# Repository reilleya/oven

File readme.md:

# Oven Controller
This repository contains the KiCAD PCB design and rust firmware for an oven controller intended for use in custom composite curing ovens.

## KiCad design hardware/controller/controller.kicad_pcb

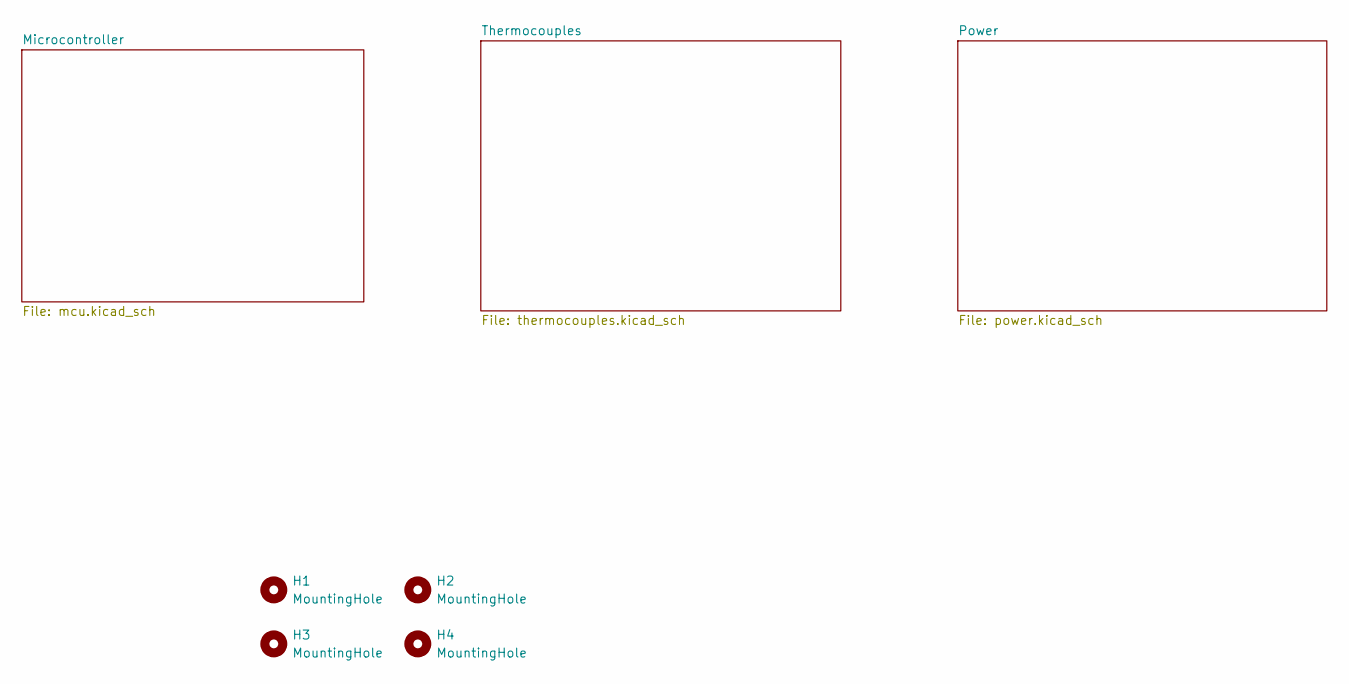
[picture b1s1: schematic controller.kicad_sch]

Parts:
H1, H2, H3, H4: MountingHole; MountingHole_2.2mm_M2_ISO14580_Pad

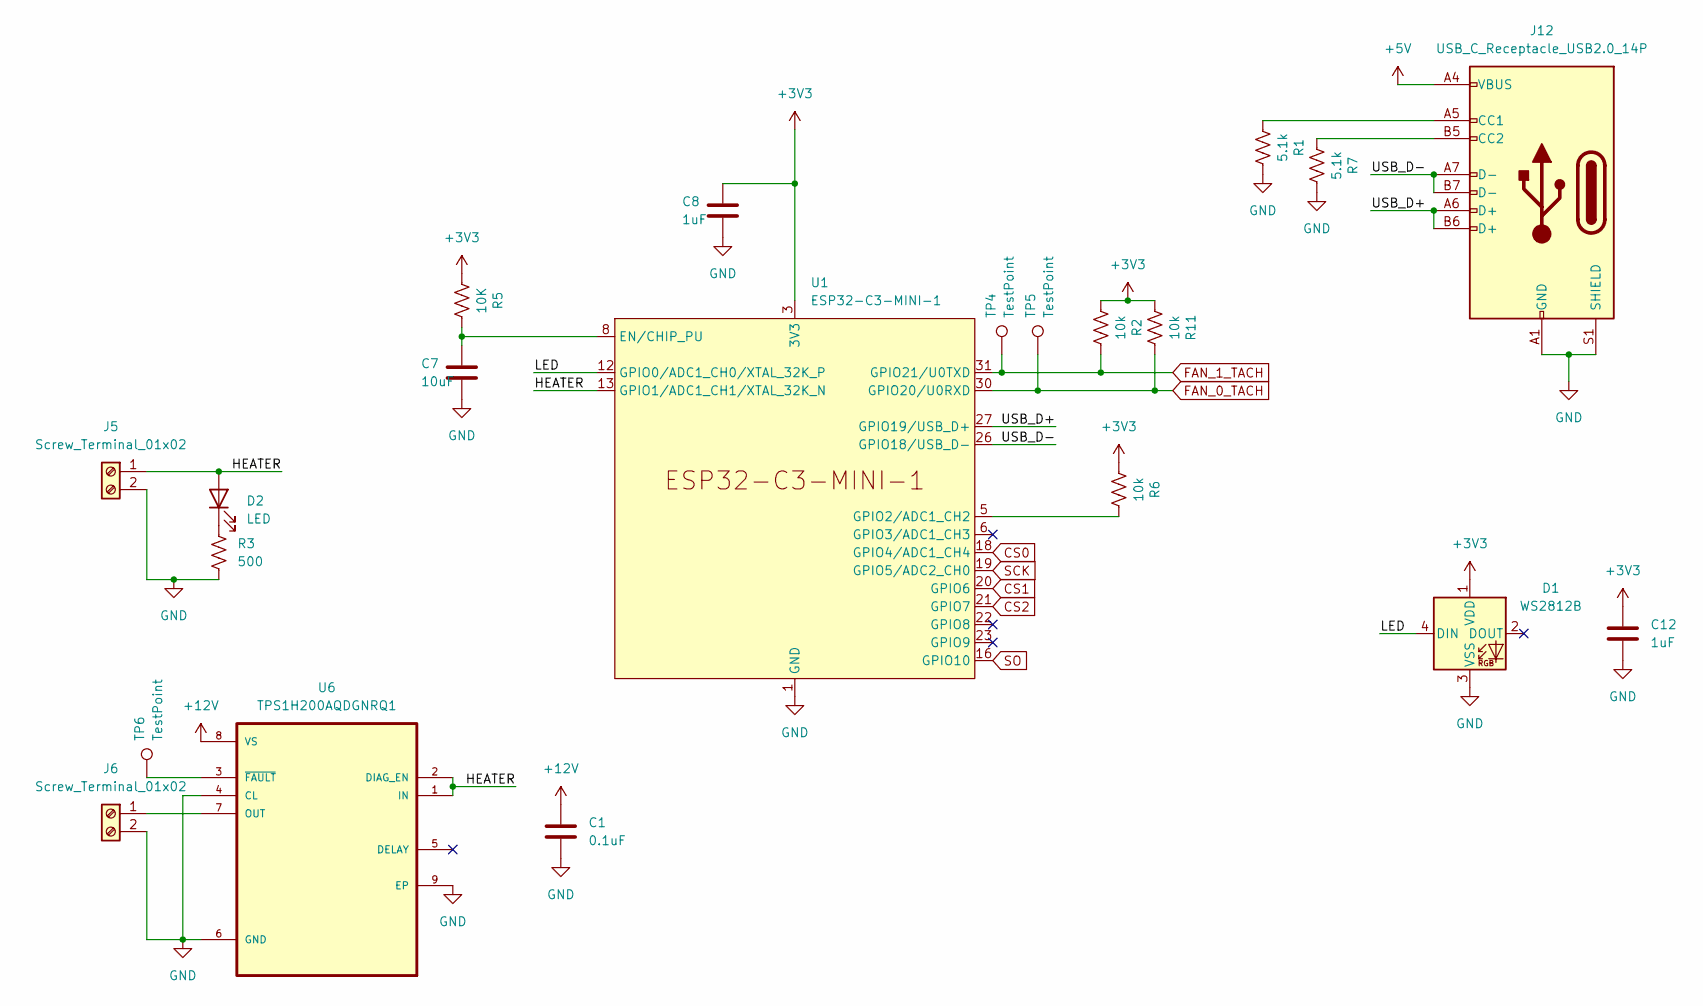
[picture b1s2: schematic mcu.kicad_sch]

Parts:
C1: 0.1uF; C_0805_2012Metric; LCSC C49678
C7: 10uF; C_0805_2012Metric; LCSC` C15850
C8, C12: 1uF; C_0805_2012Metric; LCSC C28323
D1: WS2812B; LED_WS2812B_PLCC4_5.0x5.0mm_P3.2mm; LCSC C2874885
D2: LED; LED_0805_2012Metric; LCSC C84256
J5, J6: Screw_Terminal_01x02; TerminalBlock_4Ucon_1x02_P3.50mm_Horizontal
J12: USB_C_Receptacle_USB2.0_14P; USB_C_Receptacle_GCT_USB4105-xx-A_16P_TopMnt_Horizontal; LCSC C2765186
R1, R7: 5.1k; R_0805_2012Metric; LCSC C27834
R2, R6, R11: 10k; R_0805_2012Metric; LCSC C84376
R3: 500; R_0805_2012Metric; LCSC C2828857
R5: 10K; R_0805_2012Metric; LCSC C84376
TP4, TP5, TP6: TestPoint; TestPoint_THTPad_2.0x2.0mm_Drill1.0mm
U1: ESP32-C3-MINI-1; LCSC C2838502
U6: TPS1H200AQDGNRQ1; SOP65P490X110-9N; LCSC C2653785

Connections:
+3V3: C8.1, C12.1, D1.1 (VDD), R2.2, R5.2, R6.2, R11.2, U1.3 (3V3); also elsewhere on the board
+5V: J12.A4 (VBUS), J12.A9 (VBUS), J12.B4 (VBUS), J12.B9 (VBUS); also elsewhere on the board
+12V: C1.1, U6.8 (VS); also elsewhere on the board
/Microcontroller/HEATER: D2.2 (A), J5.1, U1.13 (GPIO1/ADC1_CH1/XTAL_32K_N), U6.1 (IN), U6.2 (DIAG_EN)
/Microcontroller/LED: D1.4 (DIN), U1.12 (GPIO0/ADC1_CH0/XTAL_32K_P)
/Microcontroller/USB_D+: J12.A6 (D+), J12.B6 (D+), U1.27 (GPIO19/USB_D+)
/Microcontroller/USB_D-: J12.A7 (D-), J12.B7 (D-), U1.26 (GPIO18/USB_D-)
CS0: U1.18 (GPIO4/ADC1_CH4); also elsewhere on the board
CS1: U1.20 (GPIO6); also elsewhere on the board
CS2: U1.21 (GPIO7); also elsewhere on the board
FAN_0_TACH: R11.1, TP5.1, U1.30 (GPIO20/U0RXD); also elsewhere on the board
FAN_1_TACH: R2.1, TP4.1, U1.31 (GPIO21/U0TXD); also elsewhere on the board
GND: C1.2, C7.2, C8.2, C12.2, D1.3 (VSS), J5.2, J6.2, J12.A1 (GND), J12.A12 (GND), J12.B1 (GND), J12.B12 (GND), J12.S1 (SHIELD), R1.1, R3.2, R7.1, U1.1 (GND), U1.2 (GND), U1.11 (GND), U1.14 (GND), U1.36 (GND), U1.37 (GND), U1.38 (GND), U1.39 (GND), U1.40 (GND), U1.41 (GND), U1.42 (GND), U1.43 (GND), U1.44 (GND), U1.45 (GND), U1.46 (GND), U1.47 (GND), U1.48 (GND), U1.49 (GND), U1.50 (GND), U1.51 (GND), U1.52 (GND), U1.53 (GND), U6.4 (CL), U6.6 (GND), U6.9 (EP); also elsewhere on the board
unnamed: D2.1 (K), R3.1
unnamed: J6.1, U6.7 (OUT)
unnamed: J12.A5 (CC1), R1.2
unnamed: J12.B5 (CC2), R7.2
unnamed: C7.1, R5.1, U1.8 (EN/CHIP_PU)
unnamed: R6.1, U1.5 (GPIO2/ADC1_CH2)
unnamed: TP6.1, U6.3 (~FAULT)
SCK: U1.19 (GPIO5/ADC2_CH0); also elsewhere on the board
SO: U1.16 (GPIO10); also elsewhere on the board

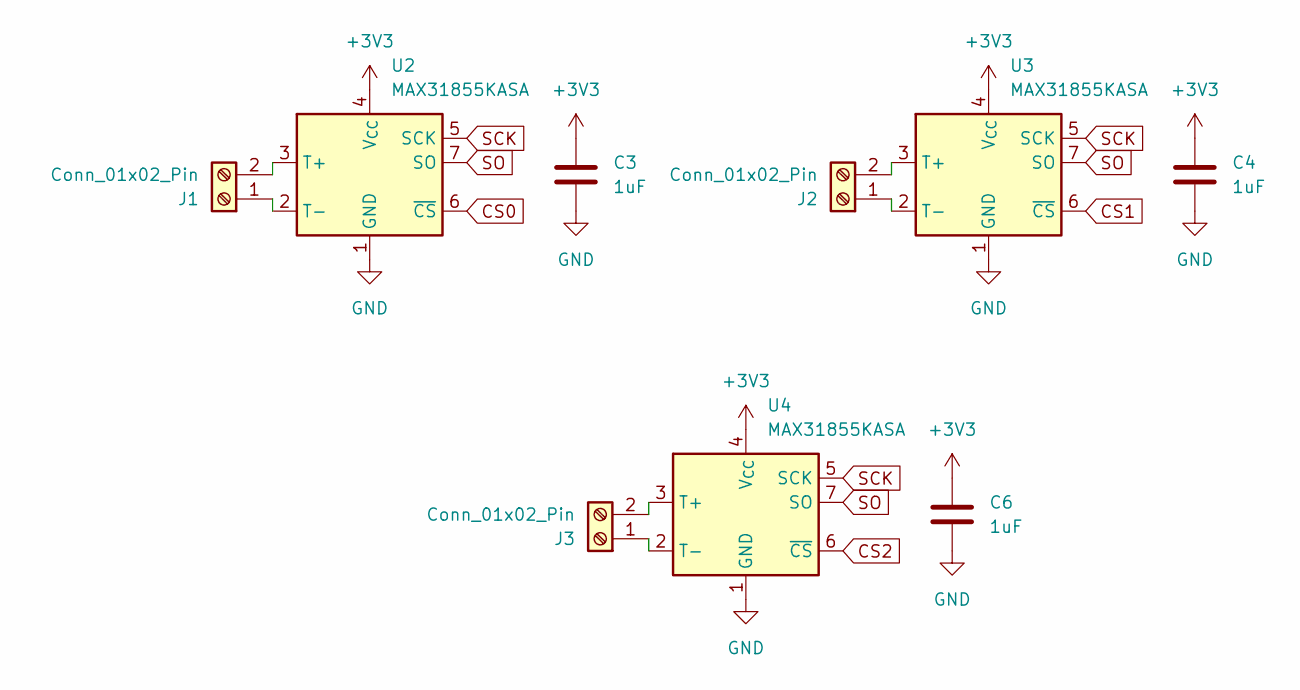
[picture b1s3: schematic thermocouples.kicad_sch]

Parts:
C3, C4, C6: 1uF; C_0805_2012Metric; LCSC C28323
J1, J2, J3: Conn_01x02_Pin; TerminalBlock_4Ucon_1x02_P3.50mm_Horizontal
U2, U3, U4: MAX31855KASA; SOIC-8_3.9x4.9mm_P1.27mm; LCSC C52028

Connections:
+3V3: C3.1, C4.1, C6.1, U2.4 (V_{CC}), U3.4 (V_{CC}), U4.4 (V_{CC}); also elsewhere on the board
CS0: U2.6 (~CS); also elsewhere on the board
CS1: U3.6 (~CS); also elsewhere on the board
CS2: U4.6 (~CS); also elsewhere on the board
GND: C3.2, C4.2, C6.2, U2.1 (GND), U3.1 (GND), U4.1 (GND); also elsewhere on the board
unnamed: J1.1, U2.2 (T-)
unnamed: J1.2, U2.3 (T+)
unnamed: J2.1, U3.2 (T-)
unnamed: J2.2, U3.3 (T+)
unnamed: J3.1, U4.2 (T-)
unnamed: J3.2, U4.3 (T+)
SCK: U2.5 (SCK), U3.5 (SCK), U4.5 (SCK); also elsewhere on the board
SO: U2.7 (SO), U3.7 (SO), U4.7 (SO); also elsewhere on the board

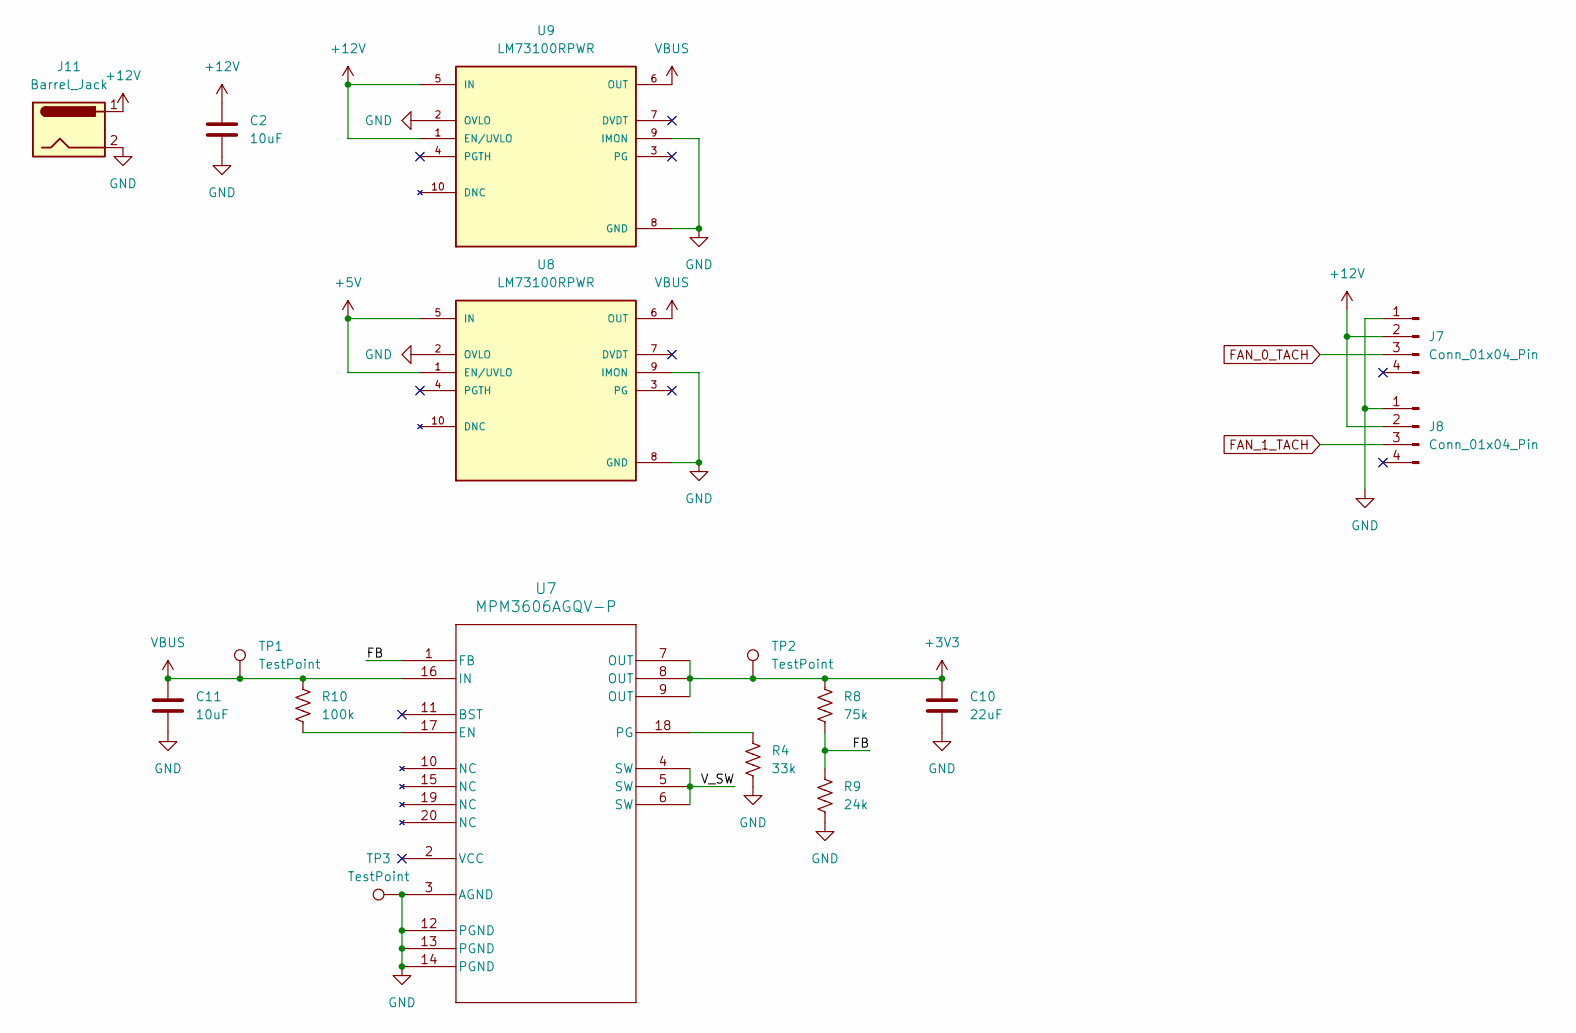
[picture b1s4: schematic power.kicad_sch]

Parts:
C2, C11: 10uF; C_0805_2012Metric; LCSC C15850
C10: 22uF; C_0805_2012Metric; LCSC C602037
J7, J8: Conn_01x04_Pin; FanPinHeader_1x04_P2.54mm_Vertical
J11: Barrel_Jack; BarrelJack_CUI_PJ-063AH_Horizontal
R4: 33k; R_0805_2012Metric; LCSC C17633
R8: 75k; R_0805_2012Metric; LCSC C17819
R9: 24k; R_0805_2012Metric; LCSC C17575
R10: 100k; R_0805_2012Metric; LCSC C96346
TP1, TP2, TP3: TestPoint; TestPoint_THTPad_2.0x2.0mm_Drill1.0mm
U7: MPM3606AGQV-P; QFN3p0x5p0x1p6_MPM3606A_MNP; LCSC C7305220
U8, U9: LM73100RPWR; IC_LM73100RPWR; PARTREV 08/2019; LCSC C3210761

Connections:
+3V3: C10.1, R8.1, TP2.1, U7.7 (OUT), U7.8 (OUT), U7.9 (OUT); also elsewhere on the board
+5V: U8.1 (EN/UVLO), U8.5 (IN); also elsewhere on the board
+12V: C2.1, J7.2, J8.2, J11.1, U9.1 (EN/UVLO), U9.5 (IN); also elsewhere on the board
/Power/FB: R8.2, R9.1, U7.1 (FB)
/Power/V_SW: U7.4 (SW), U7.5 (SW), U7.6 (SW)
FAN_0_TACH: J7.3; also elsewhere on the board
FAN_1_TACH: J8.3; also elsewhere on the board
GND: C2.2, C10.2, C11.2, J7.1, J8.1, J11.2, R4.2, R9.2, TP3.1, U7.3 (AGND), U7.12 (PGND), U7.13 (PGND), U7.14 (PGND), U8.2 (OVLO), U8.8 (GND), U8.9 (IMON), U9.2 (OVLO), U9.8 (GND), U9.9 (IMON); also elsewhere on the board
unnamed: R10.2, U7.17 (EN)
unnamed: R4.1, U7.18 (PG)
VBUS: C11.1, R10.1, TP1.1, U7.16 (IN), U8.6 (OUT), U9.6 (OUT)

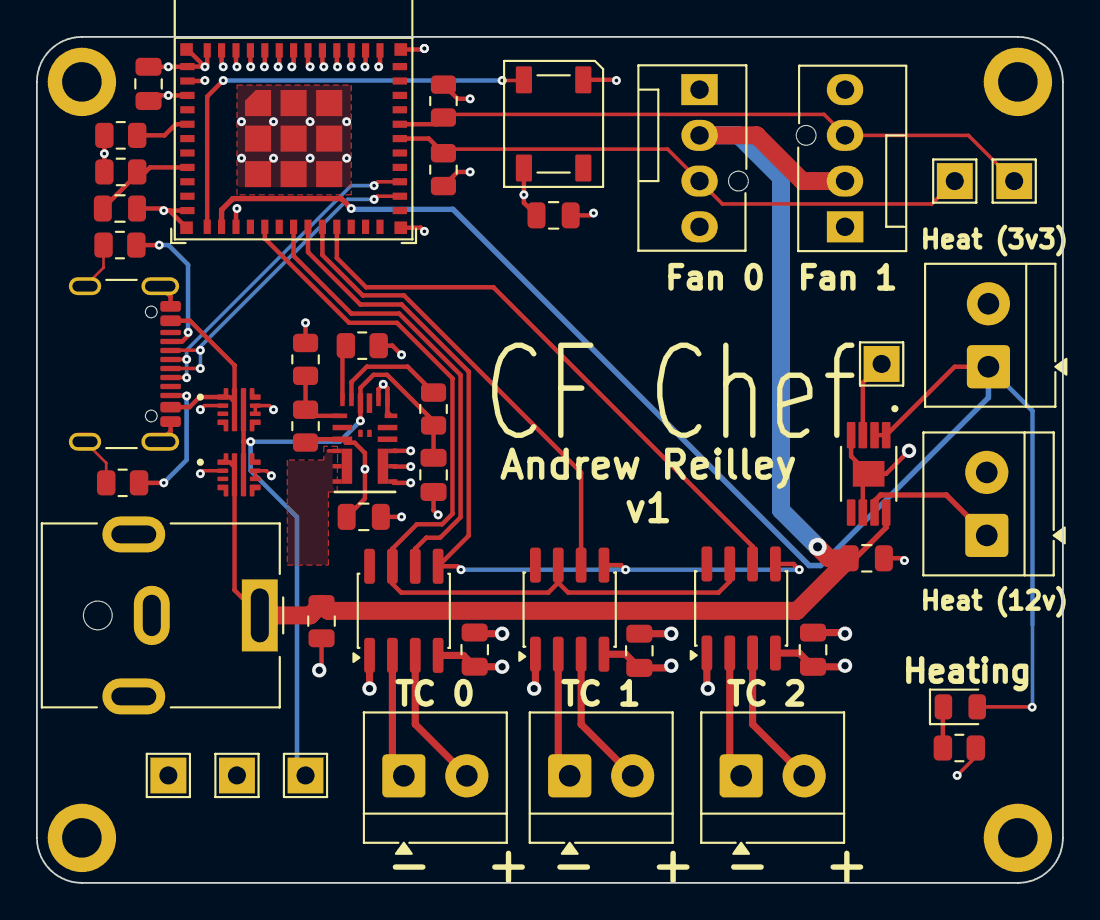
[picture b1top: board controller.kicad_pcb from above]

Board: 4 copper layers, 57.0 x 47.0 mm, 50 parts (0 on the bottom side), 33 nets.

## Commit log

2025-11-10 Initial commit, empty firmware and hardware projects
2025-11-10 Add readme, hardware gitignore
2025-11-10 First sketch of thermocouple/microcontroller hardware design
2025-11-10 Fixed up MCU strapping pins
2025-11-11 Filled out power section of schematic
2025-11-11 Get esp-hal wifi AP example working
2025-11-15 Fix USB symbol, adjust decoupling caps
2025-11-15 Drop to 3x thermocouples, 2x fans
2025-11-15 Add more decoupling caps
2025-11-22 Add wifi.rs, move setup there
2025-11-23 Added proper webserver
2025-11-23 Format code
2025-11-28 Progress
2025-12-05 Added form parsing
2025-12-07 First stab at board routing
2025-12-09 Layout tweaks
2025-12-14 Rounded corners, fixed up labels
2025-12-14 Reroute USB connector
2025-12-14 Fix some DRC errors
2025-12-15 Zain PCB review
2025-12-16 Route missed trace, add some vias
2025-12-20 Add LCSC numbers
2025-12-20 Update some LCSC numbers
2025-12-28 Update LED LCSC
2025-12-31 Add serial number box
2026-01-03 Update component position offsets for JLC
2026-01-03 Update vias to larger size for manufacturing
2026-01-14 it's past my bedtime
2026-01-15 Fix resistor on regulator, space out fan headers more
